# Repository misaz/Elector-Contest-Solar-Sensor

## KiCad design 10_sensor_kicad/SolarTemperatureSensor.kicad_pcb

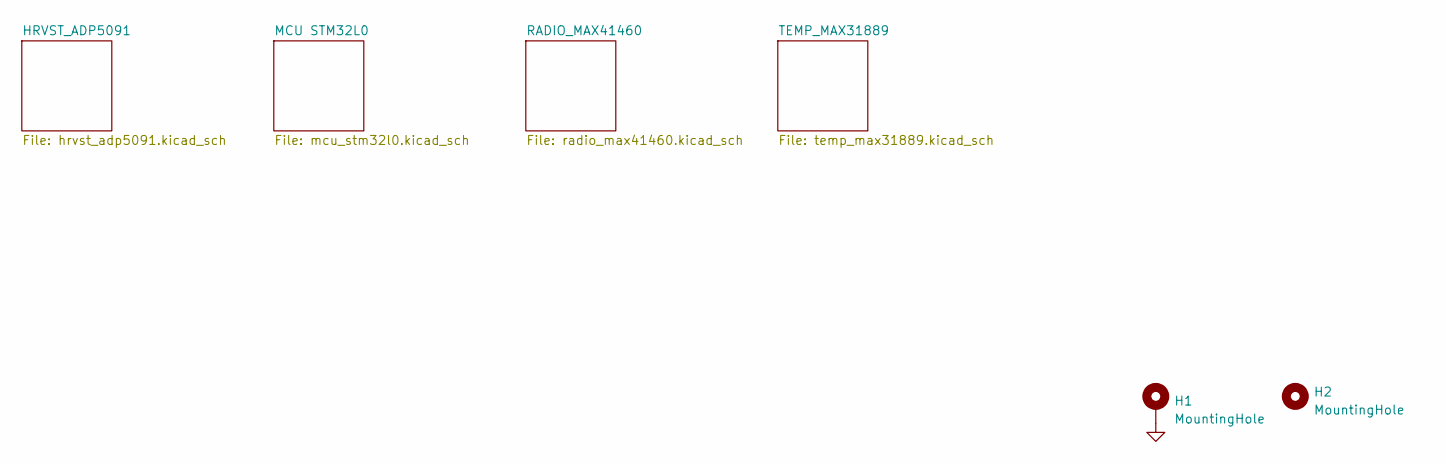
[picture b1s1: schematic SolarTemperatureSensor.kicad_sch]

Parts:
H1: MountingHole; MountingHole_3.5mm_Pad
H2: MountingHole; MountingHole_3.5mm

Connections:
GND: H1.1; also elsewhere on the board

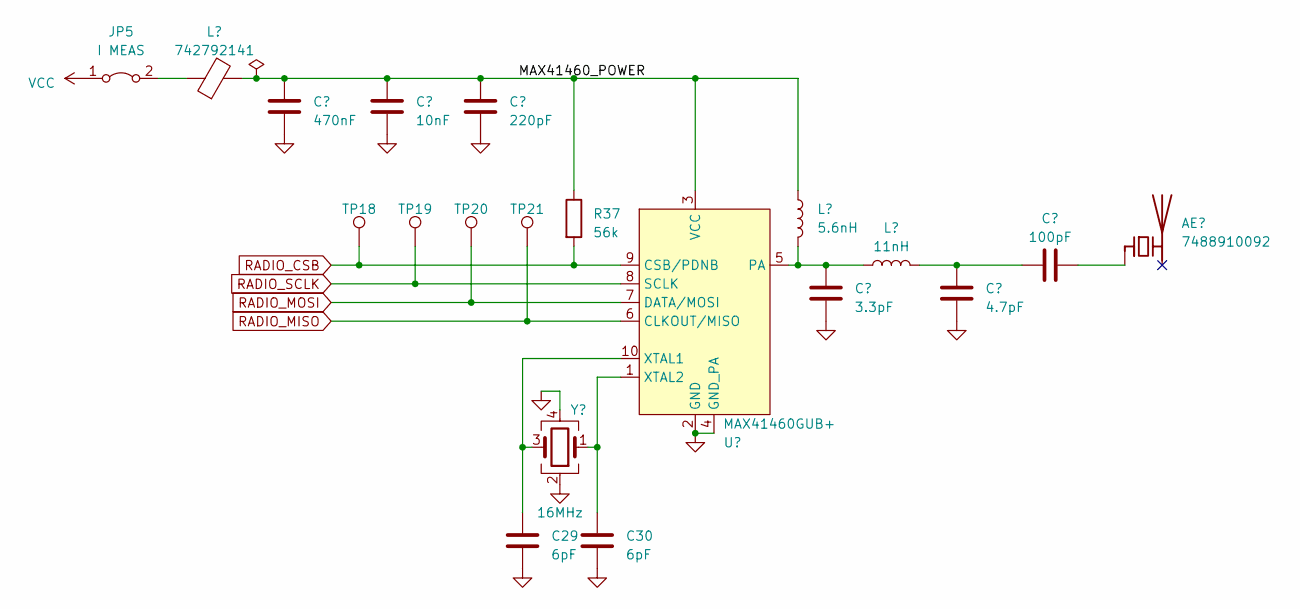
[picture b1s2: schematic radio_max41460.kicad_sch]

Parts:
AE1: 7488910092
C22: 470nF; C_0603_1608Metric_Pad1.08x0.95mm_HandSolder
C23: 10nF; C_0603_1608Metric_Pad1.08x0.95mm_HandSolder
C24: 220pF; C_0603_1608Metric_Pad1.08x0.95mm_HandSolder
C25: 3.3pF; C_0805_2012Metric_Pad1.18x1.45mm_HandSolder
C26: 4.7pF; C_0805_2012Metric_Pad1.18x1.45mm_HandSolder
C27: 100pF; C_0805_2012Metric_Pad1.18x1.45mm_HandSolder
C29, C30: 6pF; C_0805_2012Metric
JP5: I MEAS; PinHeader_1x02_P2.54mm_Vertical
L1: 5.6nH; L_0603_1608Metric_Pad1.05x0.95mm_HandSolder
L2: 11nH; L_0603_1608Metric_Pad1.05x0.95mm_HandSolder
L5: 742792141; L_1206_3216Metric
R37: 56k; R_0603_1608Metric_Pad0.98x0.95mm_HandSolder
TP18, TP19, TP20, TP21: TestPoint; TestPoint_Pad_D1.0mm
U4: MAX41460GUB+; MAX41460
Y3: 16MHz; Crystal_SMD_2016-4Pin_2.0x1.6mm

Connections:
/RADIO_MAX41460/MAX41460_POWER: C22.1, C23.1, C24.1, L1.1, L5.2, R37.1, U4.3 (VCC)
GND: C22.2, C23.2, C24.2, C25.2, C26.2, C29.2, C30.2, U4.2 (GND), U4.4 (GND_PA), Y3.2, Y3.4; also elsewhere on the board
unnamed: AE1.1 (FEED), C27.2
unnamed: C26.1, C27.1, L2.2
unnamed: JP5.2 (B), L5.1
unnamed: C25.1, L1.2, L2.1, U4.5 (PA)
unnamed: C29.1, U4.10 (XTAL1), Y3.3
unnamed: C30.1, U4.1 (XTAL2), Y3.1
RADIO_CSB: R37.2, TP18.1, U4.9 (CSB/PDNB); also elsewhere on the board
RADIO_MISO: TP21.1, U4.6 (CLKOUT/MISO); also elsewhere on the board
RADIO_MOSI: TP20.1, U4.7 (DATA/MOSI); also elsewhere on the board
RADIO_SCLK: TP19.1, U4.8 (SCLK); also elsewhere on the board
VCC: JP5.1 (A); also elsewhere on the board

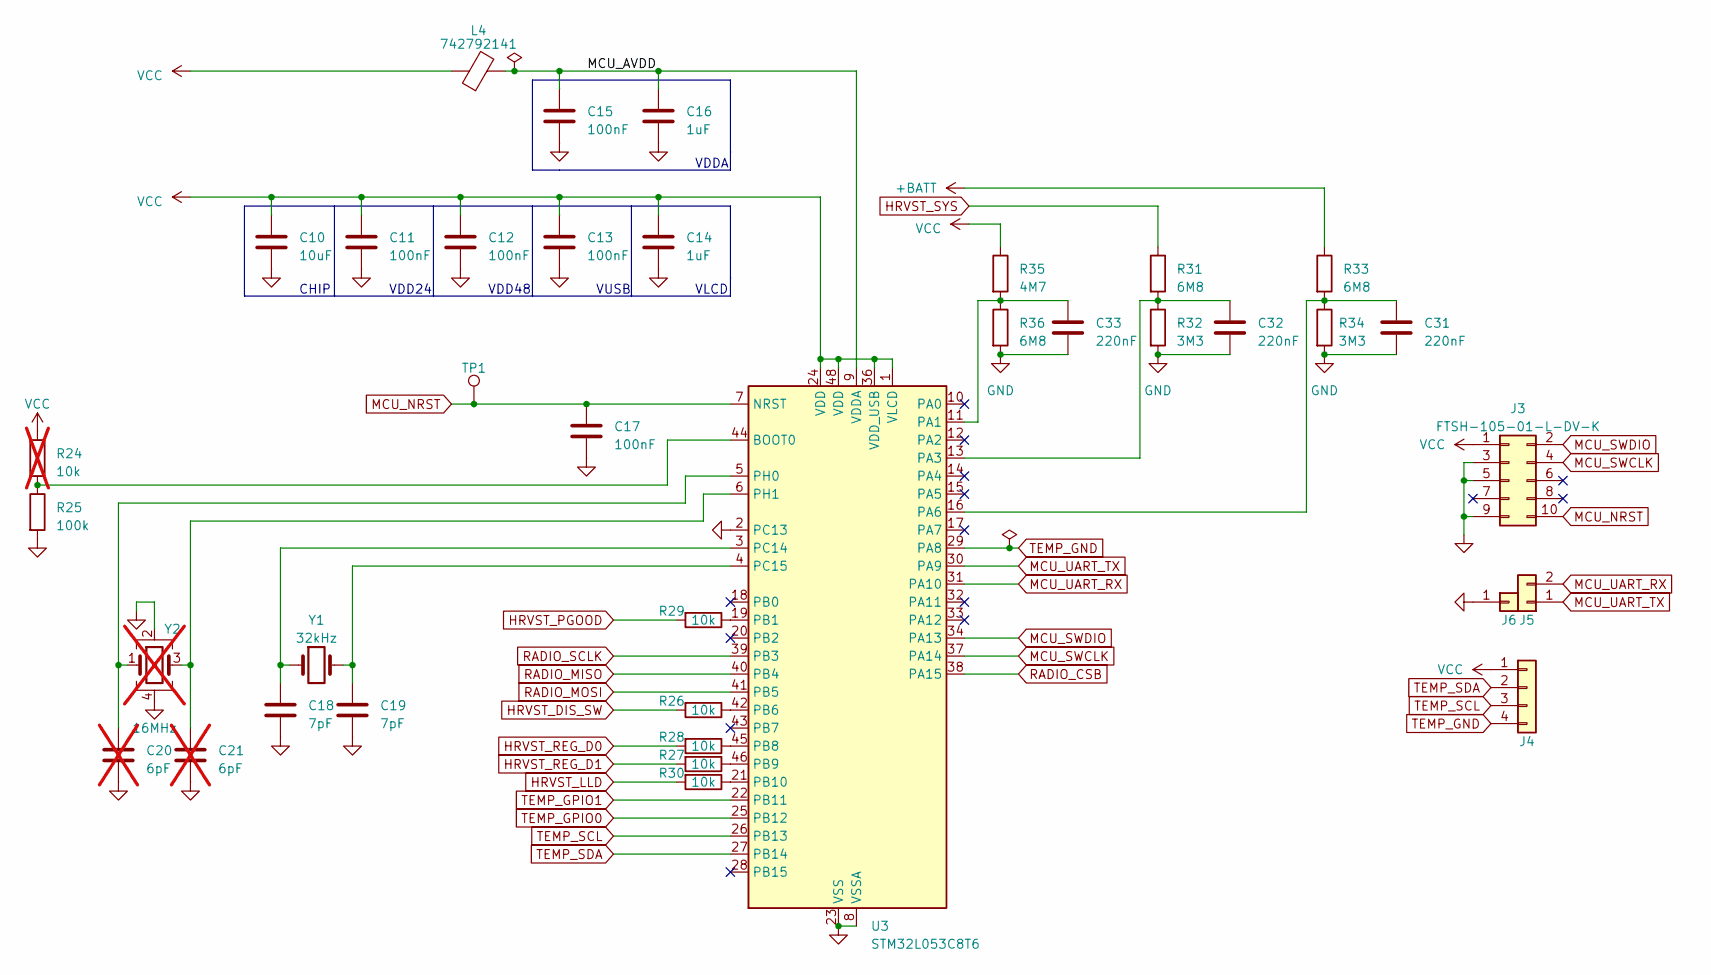
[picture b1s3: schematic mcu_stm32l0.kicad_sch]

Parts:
C10: 10uF; C_0603_1608Metric_Pad1.08x0.95mm_HandSolder
C11, C12, C13, C15, C17: 100nF; C_0603_1608Metric_Pad1.08x0.95mm_HandSolder
C14, C16: 1uF; C_0603_1608Metric_Pad1.08x0.95mm_HandSolder
C18, C19: 7pF; C_0805_2012Metric
C20, C21: 6pF; C_0805_2012Metric; not fitted
C31, C32, C33: 220nF
J3: FTSH-105-01-L-DV-K; SAMTEC_FTSH-105-XX-X-DV
J4: Conn_01x04; PinHeader_1x04_P2.54mm_Vertical
J5: Conn_01x02; PinHeader_1x02_P2.54mm_Vertical
J6: Conn_01x01; PinHeader_1x01_P2.54mm_Vertical
L4: 742792141; L_1206_3216Metric
R24: 10k; R_0603_1608Metric_Pad0.98x0.95mm_HandSolder; not fitted
R25: 100k; R_0603_1608Metric_Pad0.98x0.95mm_HandSolder
R26, R27, R28, R29, R30: 10k; R_0603_1608Metric_Pad0.98x0.95mm_HandSolder
R31, R33, R36: 6M8; R_0603_1608Metric_Pad0.98x0.95mm_HandSolder
R32, R34: 3M3; R_0603_1608Metric_Pad0.98x0.95mm_HandSolder
R35: 4M7; R_0603_1608Metric_Pad0.98x0.95mm_HandSolder
TP1: TestPoint; TestPoint_Pad_D1.0mm
U3: STM32L053C8T6; LQFP-48_7x7mm_P0.5mm
Y1: 32kHz; Crystal_SMD_3215-2Pin_3.2x1.5mm
Y2: 16MHz; Crystal_SMD_2016-4Pin_2.0x1.6mm; not fitted

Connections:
+BATT: R33.1; also elsewhere on the board
/MCU STM32L0/MCU_AVDD: C15.1, C16.1, L4.2, U3.9 (VDDA)
GND: C10.2, C11.2, C12.2, C13.2, C14.2, C15.2, C16.2, C17.2, C18.2, C19.2, C20.2, C21.2, C31.2, C32.2, C33.2, J3.3, J3.5, J3.9, J6.1, R25.2, R32.2, R34.2, R36.2, U3.2 (PC13), U3.8 (VSSA), U3.23 (VSS), U3.35 (VSS), U3.47 (VSS), Y2.2, Y2.4; also elsewhere on the board
HRVST_DIS_SW: R26.2; also elsewhere on the board
HRVST_LLD: R30.2; also elsewhere on the board
HRVST_PGOOD: R29.2; also elsewhere on the board
HRVST_REG_D0: R28.2; also elsewhere on the board
HRVST_REG_D1: R27.2; also elsewhere on the board
HRVST_SYS: R31.1; also elsewhere on the board
MCU_NRST: C17.1, J3.10, TP1.1, U3.7 (NRST)
MCU_SWCLK: J3.4, U3.37 (PA14)
MCU_SWDIO: J3.2, U3.34 (PA13)
MCU_UART_RX: J5.2, U3.31 (PA10)
MCU_UART_TX: J5.1, U3.30 (PA9)
unnamed: R24.2, R25.1, U3.44 (BOOT0)
unnamed: C33.1, R35.2, R36.1, U3.11 (PA1)
unnamed: C32.1, R31.2, R32.1, U3.13 (PA3)
unnamed: C31.1, R33.2, R34.1, U3.16 (PA6)
unnamed: R29.1, U3.19 (PB1)
unnamed: R26.1, U3.42 (PB6)
unnamed: R28.1, U3.45 (PB8)
unnamed: R27.1, U3.46 (PB9)
unnamed: R30.1, U3.21 (PB10)
unnamed: C18.1, U3.3 (PC14), Y1.1
unnamed: C19.1, U3.4 (PC15), Y1.2
unnamed: C20.1, U3.5 (PH0), Y2.1
unnamed: C21.1, U3.6 (PH1), Y2.3
RADIO_CSB: U3.38 (PA15); also elsewhere on the board
RADIO_MISO: U3.40 (PB4); also elsewhere on the board
RADIO_MOSI: U3.41 (PB5); also elsewhere on the board
RADIO_SCLK: U3.39 (PB3); also elsewhere on the board
TEMP_GND: J4.4, U3.29 (PA8); also elsewhere on the board
TEMP_GPIO0: U3.25 (PB12); also elsewhere on the board
TEMP_GPIO1: U3.22 (PB11); also elsewhere on the board
TEMP_SCL: J4.3, U3.26 (PB13); also elsewhere on the board
TEMP_SDA: J4.2, U3.27 (PB14); also elsewhere on the board
VCC: C10.1, C11.1, C12.1, C13.1, C14.1, J3.1, J4.1, L4.1, R24.1, R35.1, U3.1 (VLCD), U3.24 (VDD), U3.36 (VDD_USB), U3.48 (VDD); also elsewhere on the board

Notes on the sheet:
VDD48
CHIP
VUSB
VDD24
VLCD
VDDA

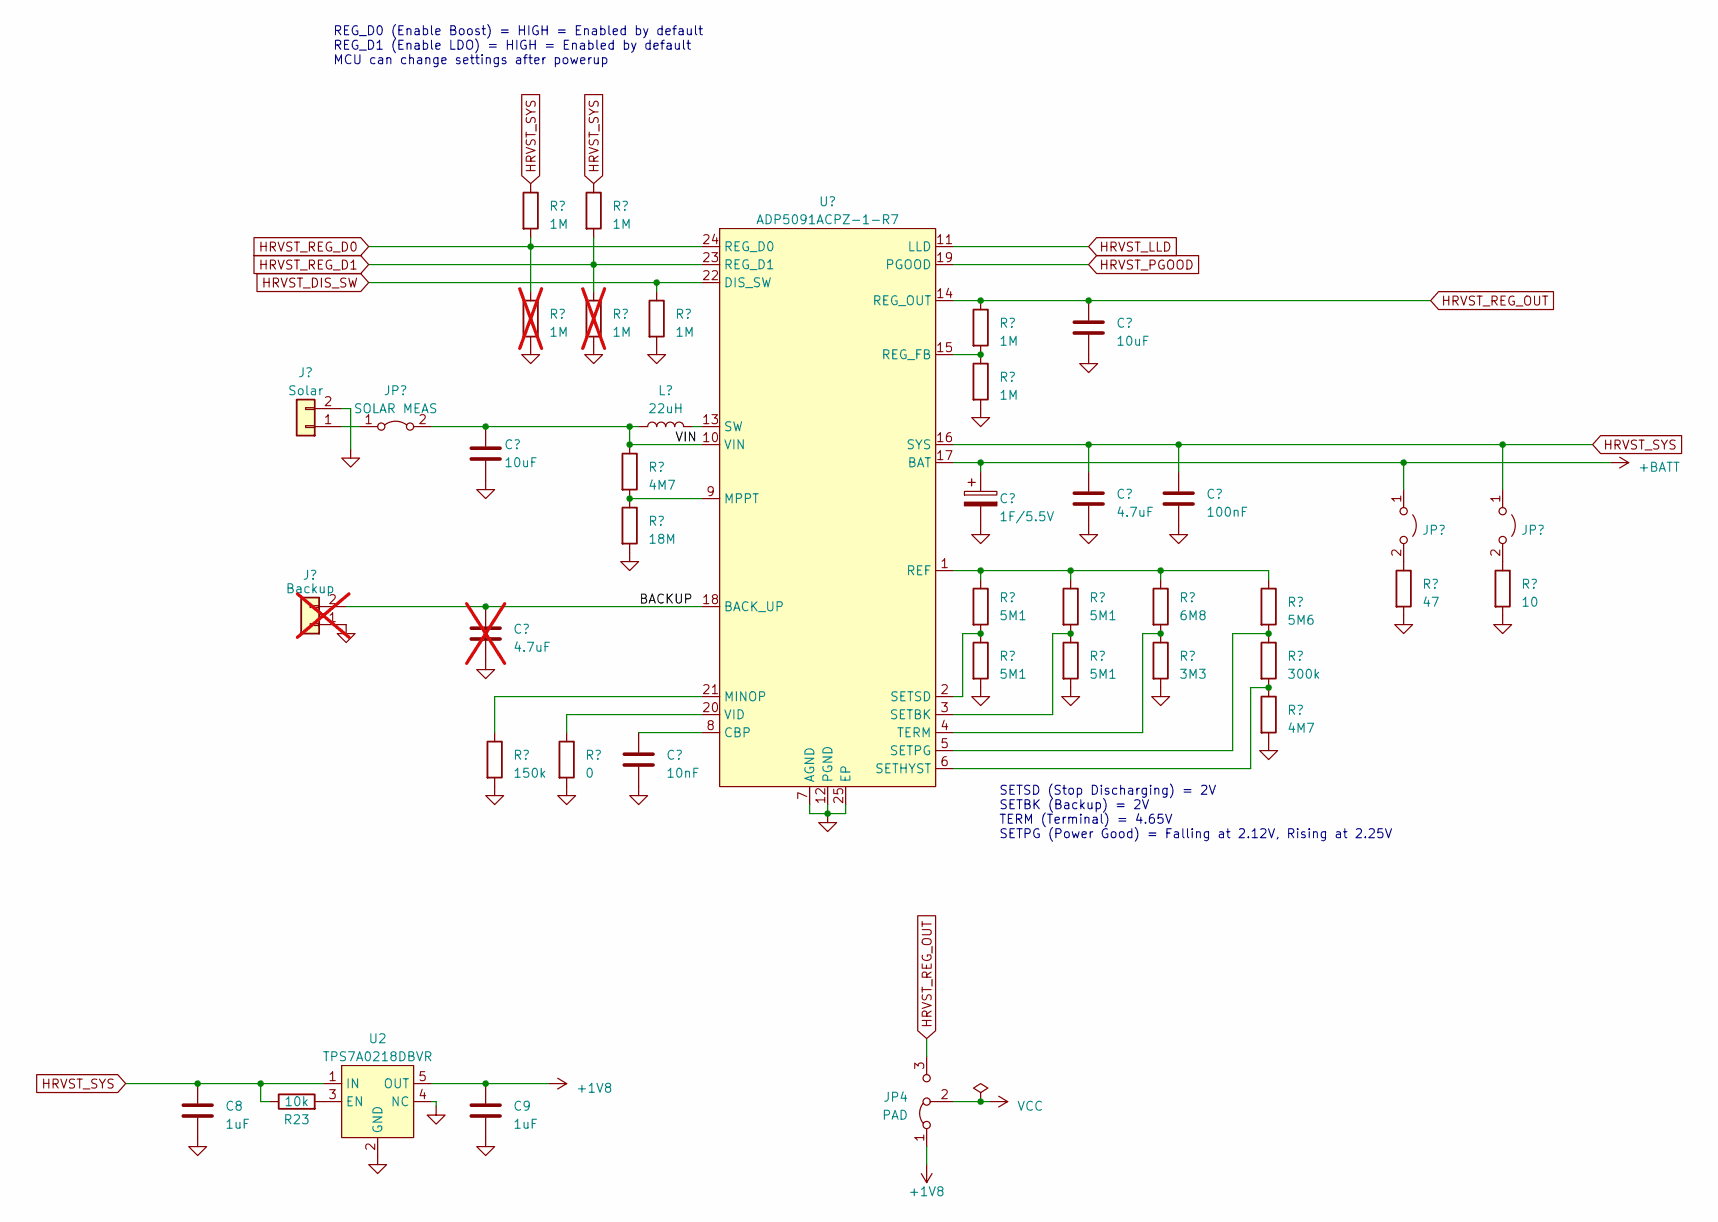
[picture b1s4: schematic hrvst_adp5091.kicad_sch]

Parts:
C1, C2: 10uF; C_0603_1608Metric_Pad1.08x0.95mm_HandSolder
C3: 1F/5.5V; SCMR18C105PRBA0
C4: 4.7uF; C_0603_1608Metric_Pad1.08x0.95mm_HandSolder
C5: 100nF; C_0603_1608Metric_Pad1.08x0.95mm_HandSolder
C6: 10nF; C_0603_1608Metric_Pad1.08x0.95mm_HandSolder
C7: 4.7uF; C_0603_1608Metric_Pad1.08x0.95mm_HandSolder; not fitted
C8, C9: 1uF; C_0603_1608Metric_Pad1.08x0.95mm_HandSolder
J1: Solar; VN02A1500000G
J2: Backup; VN02A1500000G; not fitted
JP1: SOLAR MEAS; PinHeader_1x02_P2.54mm_Vertical
JP2, JP3: BAT DISCHARGE; PinHeader_1x02_P2.54mm_Vertical
JP4: PAD; SolderJumper-3_P1.3mm_Open_RoundedPad1.0x1.5mm
L3: 22uH; DJNR6045
R1, R13: 4M7; R_0603_1608Metric_Pad0.98x0.95mm_HandSolder
R2: 18M; R_0603_1608Metric_Pad0.98x0.95mm_HandSolder
R3, R4, R18, R20, R22: 1M; R_0603_1608Metric_Pad0.98x0.95mm_HandSolder
R5, R6, R7, R8: 5M1; R_0603_1608Metric_Pad0.98x0.95mm_HandSolder
R9: 6M8; R_0603_1608Metric_Pad0.98x0.95mm_HandSolder
R10: 3M3; R_0603_1608Metric_Pad0.98x0.95mm_HandSolder
R11: 5M6; R_0603_1608Metric_Pad0.98x0.95mm_HandSolder
R12: 300k; R_0603_1608Metric_Pad0.98x0.95mm_HandSolder
R14: 150k; R_0603_1608Metric_Pad0.98x0.95mm_HandSolder
R15: 0; R_0603_1608Metric_Pad0.98x0.95mm_HandSolder
R16: 47; R_0603_1608Metric_Pad0.98x0.95mm_HandSolder
R17: 10; R_0603_1608Metric_Pad0.98x0.95mm_HandSolder
R19, R21: 1M; R_0603_1608Metric_Pad0.98x0.95mm_HandSolder; not fitted
R23: 10k; R_0603_1608Metric_Pad0.98x0.95mm_HandSolder
U1: ADP5091ACPZ-1-R7; ADP5091ACPZ-1-R7_ADI-M
U2: TPS7A0218DBVR; SOT-23-5_HandSoldering

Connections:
+1V8: C9.1, JP4.1 (A), U2.5 (OUT)
+BATT: C3.1, JP2.1 (A), U1.17 (BAT); also elsewhere on the board
/HRVST_ADP5091/BACKUP: C7.1, J2.2, U1.18 (BACK_UP)
/HRVST_ADP5091/VIN: C1.1, JP1.2 (B), L3.1, R1.1, U1.10 (VIN)
GND: C1.2, C2.2, C3.2, C4.2, C5.2, C6.2, C7.2, C8.2, C9.2, J1.2, J2.1, R2.2, R4.2, R6.2, R8.2, R10.2, R13.2, R14.2, R15.2, R16.2, R17.2, R19.2, R21.2, R22.2, U1.7 (AGND), U1.12 (PGND), U1.25 (EP), U2.2 (GND), U2.4 (NC); also elsewhere on the board
HRVST_DIS_SW: R22.1, U1.22 (DIS_SW); also elsewhere on the board
HRVST_LLD: U1.11 (LLD); also elsewhere on the board
HRVST_PGOOD: U1.19 (PGOOD); also elsewhere on the board
HRVST_REG_D0: R18.2, R19.1, U1.24 (REG_D0); also elsewhere on the board
HRVST_REG_D1: R20.2, R21.1, U1.23 (REG_D1); also elsewhere on the board
HRVST_REG_OUT: C2.1, JP4.3 (B), R3.1, U1.14 (REG_OUT)
HRVST_SYS: C4.1, C5.1, C8.1, JP3.1 (A), R18.1, R20.1, R23.1, U1.16 (SYS), U2.1 (IN); also elsewhere on the board
unnamed: J1.1, JP1.1 (A)
unnamed: JP2.2 (B), R16.1
unnamed: JP3.2 (B), R17.1
unnamed: C6.1, U1.8 (CBP)
unnamed: R14.1, U1.21 (MINOP)
unnamed: R1.2, R2.1, U1.9 (MPPT)
unnamed: R5.1, R7.1, R9.1, R11.1, U1.1 (REF)
unnamed: R3.2, R4.1, U1.15 (REG_FB)
unnamed: R7.2, R8.1, U1.3 (SETBK)
unnamed: R12.2, R13.1, U1.6 (SETHYST)
unnamed: R11.2, R12.1, U1.5 (SETPG)
unnamed: R5.2, R6.1, U1.2 (SETSD)
unnamed: L3.2, U1.13 (SW)
unnamed: R9.2, R10.1, U1.4 (TERM)
unnamed: R15.1, U1.20 (VID)
unnamed: R23.2, U2.3 (EN)
VCC: JP4.2 (C); also elsewhere on the board

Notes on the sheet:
SETSD (Stop Discharging) = 2V SETBK (Backup) = 2V TERM (Terminal) = 4.65V SETPG (Power Good) = Falling at 2.12V, Rising at 2.25V
REG_D0 (Enable Boost) = HIGH = Enabled by default REG_D1 (Enable LDO) = HIGH = Enabled by default MCU can change settings after powerup

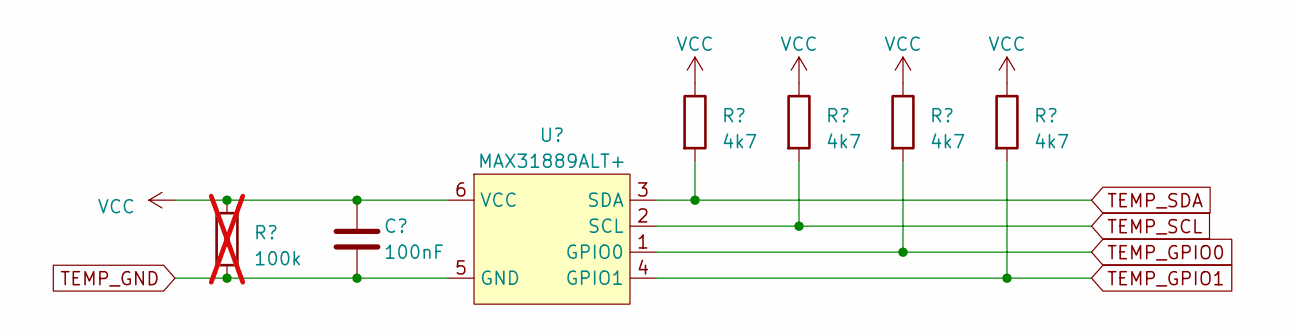
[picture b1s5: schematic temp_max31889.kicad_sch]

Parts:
C28: 100nF; C_0603_1608Metric_Pad1.08x0.95mm_HandSolder
R38, R39, R40, R41: 4k7; R_0603_1608Metric_Pad0.98x0.95mm_HandSolder
R42: 100k; R_0603_1608Metric_Pad0.98x0.95mm_HandSolder; not fitted
U5: MAX31889ALT+; MAXIM-uDFN6

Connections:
TEMP_GND: C28.2, R42.2, U5.5 (GND); also elsewhere on the board
TEMP_GPIO0: R40.2, U5.1 (GPIO0); also elsewhere on the board
TEMP_GPIO1: R41.2, U5.4 (GPIO1); also elsewhere on the board
TEMP_SCL: R39.2, U5.2 (SCL); also elsewhere on the board
TEMP_SDA: R38.2, U5.3 (SDA); also elsewhere on the board
VCC: C28.1, R38.1, R39.1, R40.1, R41.1, R42.1, U5.6 (VCC); also elsewhere on the board

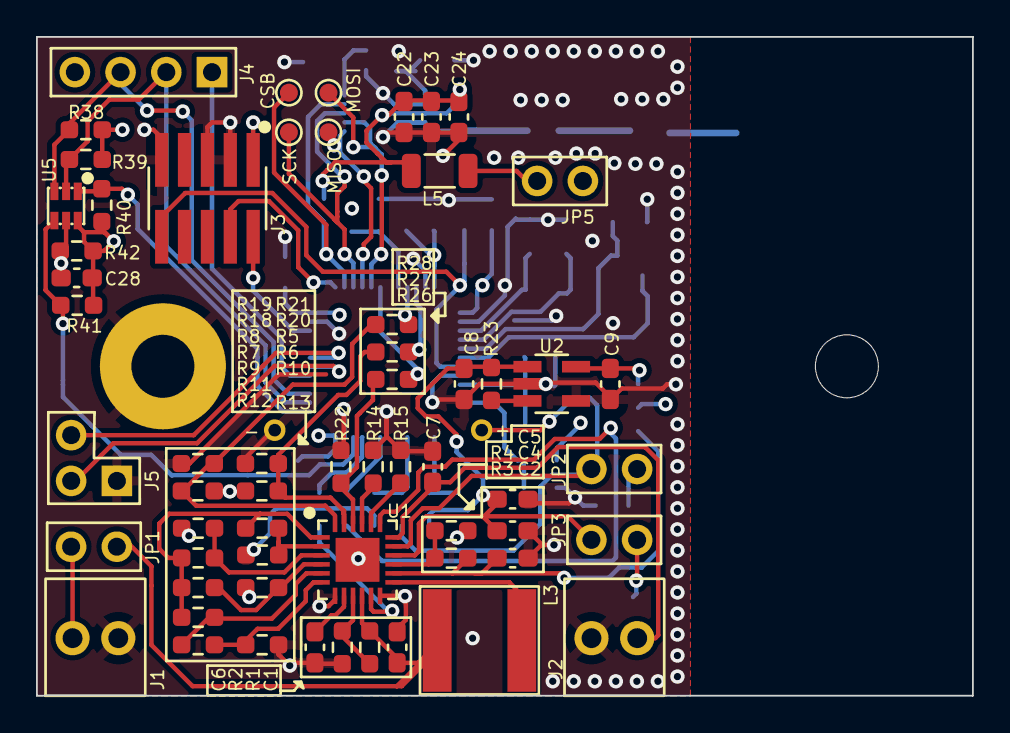
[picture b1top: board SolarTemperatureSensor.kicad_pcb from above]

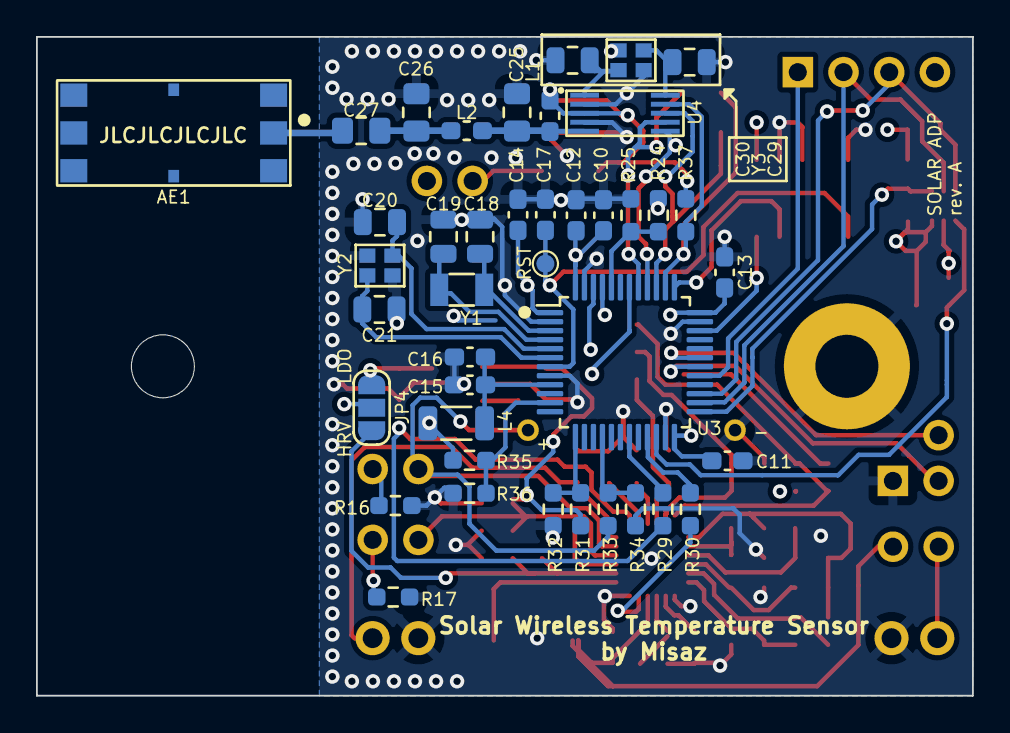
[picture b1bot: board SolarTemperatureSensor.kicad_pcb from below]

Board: 4 copper layers, 52.0 x 36.6 mm, 104 parts (41 on the bottom side), 64 nets.

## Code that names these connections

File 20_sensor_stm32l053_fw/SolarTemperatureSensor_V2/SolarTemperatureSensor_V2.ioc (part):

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Mcu.Name=STM32L053C(6-8)Tx
Mcu.Package=LQFP48
Mcu.UserName=STM32L053C8Tx
PA0.GPIOParameters=GPIO_Label
PA0.GPIO_Label=UNUSED0
PA0.Signal=GPIO_Analog
PA1.GPIOParameters=GPIO_Label
PA1.GPIO_Label=UNUSED1
PA1.Signal=GPIO_Analog
PA10.GPIOParameters=PinState,GPIO_Label
PA10.GPIO_Label=DBG2
PA10.PinState=GPIO_PIN_RESET
PA10.Signal=GPIO_Output
PA11.GPIOParameters=GPIO_Label
PA11.GPIO_Label=UNUSED6_GND
PA11.Signal=GPIO_Output
PA12.GPIOParameters=PinState,GPIO_Label
PA12.GPIO_Label=UNUSED7_GND
PA12.PinState=GPIO_PIN_RESET
PA12.Signal=GPIO_Output
PA13.Mode=Serial_Wire
PA13.Signal=SYS_SWDIO
PA14.Mode=Serial_Wire
PA14.Signal=SYS_SWCLK
PA15.GPIOParameters=PinState,GPIO_Label
PA15.GPIO_Label=RADIO_CSB
PA15.PinState=GPIO_PIN_SET
PA15.Signal=GPIO_Output
PA2.GPIOParameters=GPIO_Label
PA2.GPIO_Label=UNUSED2
PA2.Signal=GPIO_Analog
PA3.GPIOParameters=GPIO_Label
PA3.GPIO_Label=VBATT_ADC_EN
PA3.Signal=GPIO_Analog
PA4.GPIOParameters=GPIO_Label
PA4.GPIO_Label=UNUSED3
PA4.Signal=GPIO_Analog
PA5.GPIOParameters=GPIO_Label
PA5.GPIO_Label=UNUSED4
PA5.Signal=GPIO_Analog
PA6.GPIOParameters=GPIO_Label
PA6.GPIO_Label=VBATT_ADC_IN
PA6.Signal=GPIO_Analog
PA7.GPIOParameters=GPIO_Label
PA7.GPIO_Label=UNUSED5
PA7.Signal=GPIO_Analog
PA8.GPIOParameters=PinState,GPIO_Label
PA8.GPIO_Label=TEMP_GND
PA8.PinState=GPIO_PIN_SET
PA8.Signal=GPIO_Output
PA9.GPIOParameters=GPIO_Speed,PinState,GPIO_Label
PA9.GPIO_Label=DBG1
PA9.GPIO_Speed=GPIO_SPEED_FREQ_LOW
PA9.PinState=GPIO_PIN_RESET
PA9.Signal=GPIO_Output
PB0.GPIOParameters=GPIO_Label
PB0.GPIO_Label=UNUSED8
PB0.Signal=GPIO_Analog
PB1.GPIOParameters=GPIO_Label
PB1.GPIO_Label=HRVST_PGOOD
PB1.Signal=GPIO_Input
PB10.GPIOParameters=GPIO_Label
PB10.GPIO_Label=HRVST_LLD
PB10.Signal=GPIO_Input
PB11.GPIOParameters=PinState,GPIO_Label
PB11.GPIO_Label=TEMP_GPIO1
PB11.PinState=GPIO_PIN_SET
PB11.Signal=GPIO_Output
PB12.GPIOParameters=PinState,GPIO_Label
PB12.GPIO_Label=TEMP_GPIO0
PB12.PinState=GPIO_PIN_SET
PB12.Signal=GPIO_Output
PB13.Mode=I2C
PB13.Signal=I2C2_SCL
PB14.Mode=I2C
PB14.Signal=I2C2_SDA
PB15.GPIOParameters=GPIO_Label
PB15.GPIO_Label=UNUSED11_GND
PB15.Signal=GPIO_Output
PB2.GPIOParameters=GPIO_Label
PB2.GPIO_Label=UNUSED9
PB2.Signal=GPIO_Analog
PB3.GPIOParameters=GPIO_Label
PB3.GPIO_Label=RADIO_SCLK
PB3.Mode=Full_Duplex_Master
PB3.Signal=SPI1_SCK
PB4.GPIOParameters=GPIO_Label
PB4.GPIO_Label=RADIO_MISO
PB4.Mode=Full_Duplex_Master
PB4.Signal=SPI1_MISO
PB5.GPIOParameters=GPIO_Label
PB5.GPIO_Label=RADIO_MOSI
PB5.Mode=Full_Duplex_Master
PB5.Signal=SPI1_MOSI
PB6.GPIOParameters=GPIO_Label
PB6.GPIO_Label=HRVST_DIS_SW
PB6.Signal=GPIO_Output
PB7.GPIOParameters=GPIO_Label
PB7.GPIO_Label=UNUSED10_GND
PB7.Signal=GPIO_Output
PB8.GPIOParameters=PinState,GPIO_Label
PB8.GPIO_Label=HRVST_REG_D0
PB8.PinState=GPIO_PIN_SET
PB8.Signal=GPIO_Output
PB9.GPIOParameters=PinState,GPIO_Label
PB9.GPIO_Label=HRVST_REG_D1
PB9.PinState=GPIO_PIN_SET
PB9.Signal=GPIO_Output
PC13.GPIOParameters=GPIO_Label
PC13.GPIO_Label=UNUSED11
PC13.Signal=GPIO_Analog
PC14-OSC32_IN.Mode=LSE-External-Oscillator
PC14-OSC32_IN.Signal=RCC_OSC32_IN
PC15-OSC32_OUT.Mode=LSE-External-Oscillator
PC15-OSC32_OUT.Signal=RCC_OSC32_OUT
PH0-OSC_IN.GPIOParameters=GPIO_Label
PH0-OSC_IN.GPIO_Label=XTAL_16M_UNUSED1
PH0-OSC_IN.Signal=GPIO_Output
PH1-OSC_OUT.GPIOParameters=GPIO_Label
PH1-OSC_OUT.GPIO_Label=XTAL_16M_UNUSED2
PH1-OSC_OUT.Signal=GPIO_Output
RCC.HSE_VALUE=8000000
RCC.SYSCLKFreq_VALUE=524288
board=custom

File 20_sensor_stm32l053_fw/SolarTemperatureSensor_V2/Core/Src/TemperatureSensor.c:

#include "TemperatureSensor.h"
#include "App.h"

#include "stm32l0xx_hal.h"
#include "main.h"

extern I2C_HandleTypeDef hi2c2;

static int TemperatureSensor_PowerOn() {
	// set device address (GPIO0, GPIO1) and power on temperature sensor
	HAL_GPIO_WritePin(TEMP_GPIO0_GPIO_Port, TEMP_GPIO0_Pin, 1);
	HAL_GPIO_WritePin(TEMP_GPIO1_GPIO_Port, TEMP_GPIO1_Pin, 1);
	HAL_GPIO_WritePin(TEMP_GND_GPIO_Port, TEMP_GND_Pin, 0);

	// wait for sensor powerup
	App_SleepShortMs(1);

	// Init I2C Driver
	__HAL_RCC_I2C2_CLK_ENABLE();
	MX_I2C2_Init();

	return 0;
}

static int TemperatureSensor_PowerDown() {
	HAL_StatusTypeDef hStatus;

	hStatus = HAL_I2C_DeInit(&hi2c2);
	// error ignored
	(void)hStatus;

	// shutdown I2C peripheral
	__HAL_RCC_I2C2_FORCE_RESET();
	__HAL_RCC_I2C2_RELEASE_RESET();
	__HAL_RCC_I2C2_CLK_DISABLE();

	// power off the sensor
	HAL_GPIO_WritePin(TEMP_GPIO0_GPIO_Port, TEMP_GPIO0_Pin, 1);
	HAL_GPIO_WritePin(TEMP_GPIO1_GPIO_Port, TEMP_GPIO1_Pin, 1);
	HAL_GPIO_WritePin(TEMP_GND_GPIO_Port, TEMP_GND_Pin, 1);

	return 0;
}

int TemperatureSensor_BeginMeasurement() {
	int iStatus;
	HAL_StatusTypeDef hStatus;

	iStatus = TemperatureSensor_PowerOn();
	if (iStatus) {
		TemperatureSensor_PowerDown();
		return iStatus;
	}

	// read part ID
	/*
	uint8_t partId = 0;
	hStatus = HAL_I2C_Mem_Read(&hi2c2, 0xA6, 0xFF, 1, &partId, sizeof(partId), 100);
	if (hStatus) {
		TemperatureSensor_PowerDown();
		return 1;
	}
	*/

	// trigger conversion
	uint8_t tempSetup = 0xC1;
	hStatus = HAL_I2C_Mem_Write(&hi2c2, 0xA6, 0x14, 1, &tempSetup, sizeof(tempSetup), 100);
	if (hStatus) {
		TemperatureSensor_PowerDown();
		return 1;
	}

	return 0;
}


int TemperatureSensor_GetTemperature(int16_t* temperatureRaw) {
	HAL_StatusTypeDef hStatus;

	uint8_t fifoCount = 0;
	uint8_t retries = 25;
	do {
		hStatus = HAL_I2C_Mem_Read(&hi2c2, 0xA6, 0x07, 1, &fifoCount, sizeof(fifoCount), 100);
		if (hStatus) {
			TemperatureSensor_PowerDown();
			return 1;
		}

		if (fifoCount != 1) {
			App_SleepShortMs(1);
		}
	} while (fifoCount != 1 && retries--);

	if (fifoCount != 1) {
		TemperatureSensor_PowerDown();
		return 1;
	}

	// read data
	uint8_t temperatureBytes[2];
	hStatus = HAL_I2C_Mem_Read(&hi2c2, 0xA6, 0x08, 1, temperatureBytes, sizeof(temperatureBytes), 100);
	if (hStatus) {
		TemperatureSensor_PowerDown();
		return 1;
	}

	uint16_t temperatureUint = (((uint16_t) (temperatureBytes[0])) << 8) | (uint16_t) (temperatureBytes[1]);

	*temperatureRaw = (int16_t)temperatureUint;

	TemperatureSensor_PowerDown();

	return 0;
}
